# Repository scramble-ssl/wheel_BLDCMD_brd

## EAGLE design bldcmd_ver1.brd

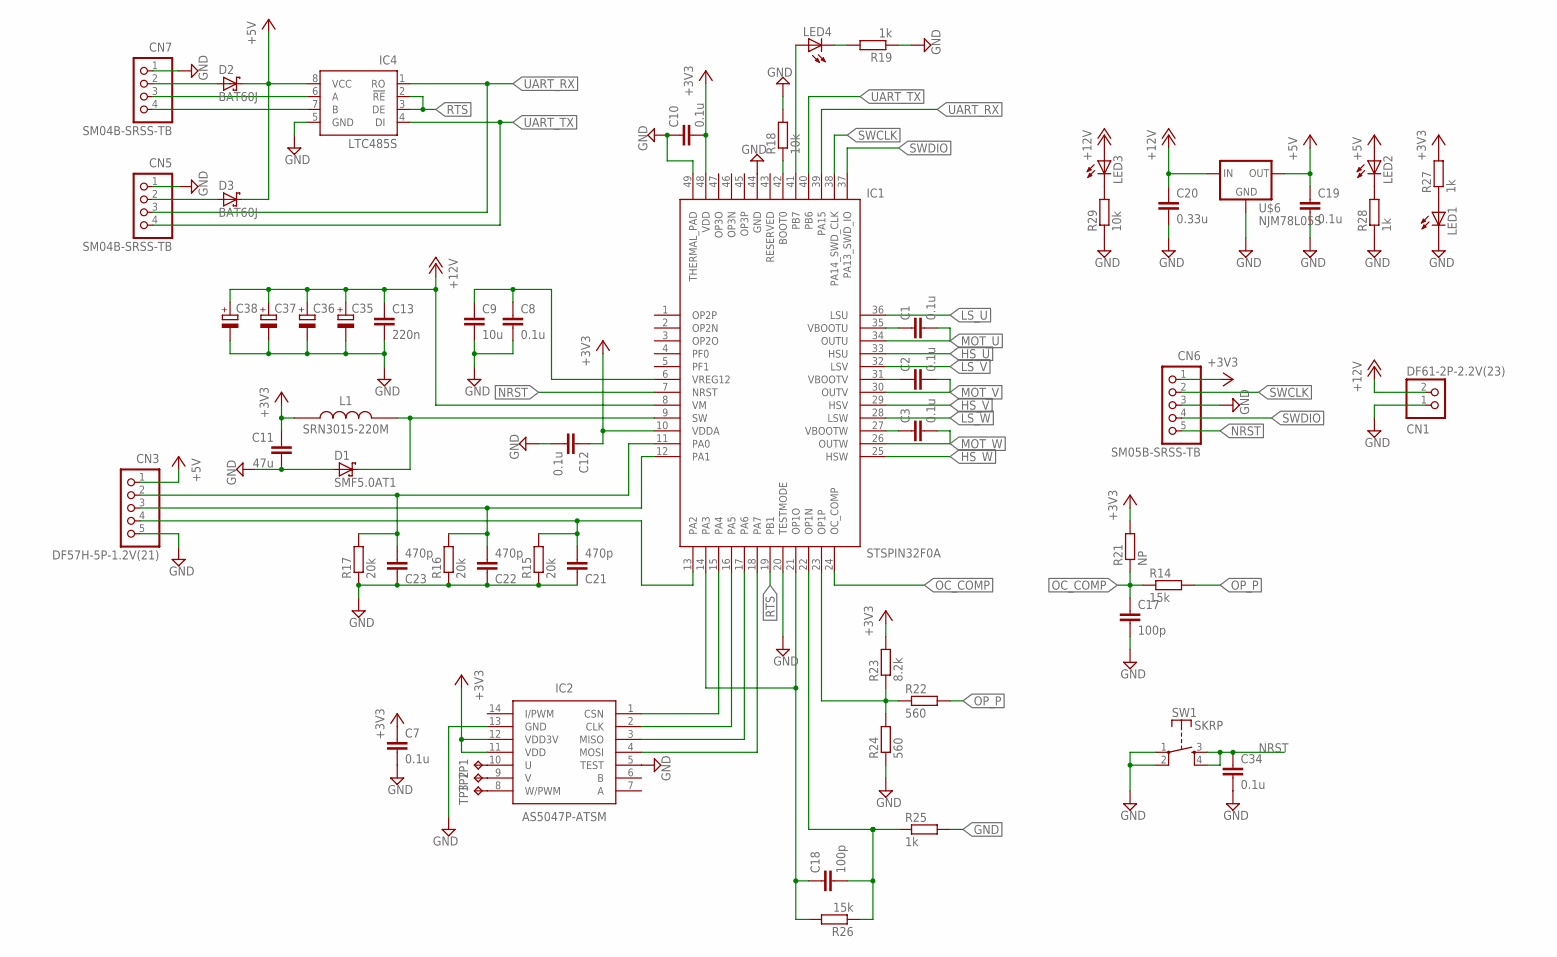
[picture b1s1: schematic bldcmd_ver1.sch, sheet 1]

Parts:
C1, C2, C3: 0.1u; C0402
C7, C8, C10, C12, C19, C34: 0.1u; C0603K
C9: 10u; C0805K
C11: 47u; C1206K
C13: 220n; C0805K
C17, C18: 100p; C0402
C20: 0.33u; C0805K
C21, C22, C23: 470p; C0402
C35, C36, C37, C38: CPOL-EU153CLV-0605; 153CLV-0605
CN1: DF61-2P-2.2V(23); DF61-2P-2.2V
CN3: DF57H-5P-1.2V(21)
CN5, CN7: SM04B-SRSS-TB
CN6: SM05B-SRSS-TB
D1: SMF5.0AT1; SOD123FL
D2, D3: BAT60J; SOD323_ST
IC1: STSPIN32F0A; VFQFPN48_7X7X1.0-48L
IC2: AS5047P-ATSM; SOP65P640X120-14N
IC4: LTC485S; SOIC8
L1: SRN3015-220M; SRN3015
LED1, LED2, LED3, LED4: LEDSML0603; SML0603
R14, R26: 15k; R0402
R15, R16, R17: 20k; R0402
R18: 10k; R0402
R19, R27, R28: 1k; R0603
R21: NP; R0402
R22, R24: 560; R0402
R23: 8.2k; R0402
R25: 1k; R0402
R29: 10k; R0603
SW1: SKRP
TP1, TP2, TP3: TPTP08R; TP08R
U$6: NJM78L05S; SOT89R

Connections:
+3V3: C7.1, C10.2, C11.1, C12.1, CN6.1, IC1.10 (VDDA), IC1.48 (VDD), IC2.11 (VDD), IC2.12 (VDD3V), L1.1, R21.2, R23.2, R27.2
+5V: C19.1, CN3.1, D2.C, D3.C, IC4.8 (VCC), LED2.A, U$6.2 (OUT)
+12V: C13.1, C20.1, C35.+, C36.+, C37.+, C38.+, CN1.2, IC1.8 (VM), LED3.A, U$6.1 (IN); also elsewhere on the board
GND: C7.2, C8.2, C9.2, C10.1, C11.2, C12.2, C13.2, C17.2, C19.2, C20.2, C21.1, C22.1, C23.1, C34.2, C35.-, C36.-, C37.-, C38.-, CN1.1, CN3.5, CN5.1, CN6.3, CN7.1, D1.A, IC1.20 (TESTMODE), IC1.44 (GND), IC1.49 (THERMAL_PAD), IC2.5 (TEST), IC2.13 (GND), IC4.5 (GND), LED1.C, R15.1, R16.1, R17.1, R18.2, R19.1, R24.1, R25.2, R28.1, R29.1, SW1.1, SW1.2, U$6.3 (GND), U$6.4 (GND); also elsewhere on the board
HS_U: IC1.33 (HSU); also elsewhere on the board
HS_V: IC1.29 (HSV); also elsewhere on the board
HS_W: IC1.25 (HSW); also elsewhere on the board
LS_U: IC1.36 (LSU); also elsewhere on the board
LS_V: IC1.32 (LSV); also elsewhere on the board
LS_W: IC1.28 (LSW); also elsewhere on the board
MOT_U: C1.2, IC1.34 (OUTU); also elsewhere on the board
MOT_V: C2.2, IC1.30 (OUTV); also elsewhere on the board
MOT_W: C3.2, IC1.26 (OUTW); also elsewhere on the board
unnamed: C3.1, IC1.27 (VBOOTW)
unnamed: IC2.10 (U), TP1.TP
unnamed: IC2.9 (V), TP2.TP
unnamed: C2.1, IC1.31 (VBOOTV)
unnamed: C1.1, IC1.35 (VBOOTU)
unnamed: IC2.8 (W/PWM), TP3.TP
unnamed: IC1.15 (PA4), IC2.1 (CSN)
unnamed: IC1.16 (PA5), IC2.2 (CLK)
unnamed: CN5.2, D3.A
unnamed: IC1.17 (PA6), IC2.3 (MISO)
unnamed: IC1.18 (PA7), IC2.4 (MOSI)
unnamed: D1.C, IC1.9 (SW), L1.2
unnamed: C8.1, C9.1, IC1.6 (VREG12)
unnamed: LED2.C, R28.2
unnamed: IC1.42 (BOOT0), R18.1
unnamed: C21.2, CN3.4, IC1.13 (PA2), R15.2
unnamed: C22.2, CN3.3, IC1.12 (PA1), R16.2
unnamed: C23.2, CN3.2, IC1.11 (PA0), R17.2
unnamed: IC1.23 (OP1P), R22.1, R23.1, R24.2
unnamed: C18.2, IC1.22 (OP1N), R25.1, R26.1
unnamed: C18.1, IC1.14 (PA3), IC1.21 (OP1O), R26.2
unnamed: CN7.3, IC4.6 (A)
unnamed: CN7.2, D2.A
unnamed: LED1.A, R27.1
unnamed: CN7.4, IC4.7 (B)
unnamed: LED4.C, R19.2
unnamed: LED3.C, R29.2
unnamed: IC1.41 (PB7), LED4.A
NRST: C34.1, CN6.5, IC1.7 (NRST), SW1.3, SW1.4
OC_COMP: C17.1, IC1.24 (OC_COMP), R14.1, R21.1
OP_P: R14.2, R22.2; also elsewhere on the board
RTS: IC1.19 (PB1), IC4.2 (!RE), IC4.3 (DE)
SWCLK: CN6.2, IC1.38 (PA14_SWD_CLK)
SWDIO: CN6.4, IC1.37 (PA13_SWD_IO)
UART_RX: CN5.3, IC1.39 (PA15), IC4.1 (RO)
UART_TX: CN5.4, IC1.40 (PB6), IC4.4 (DI)

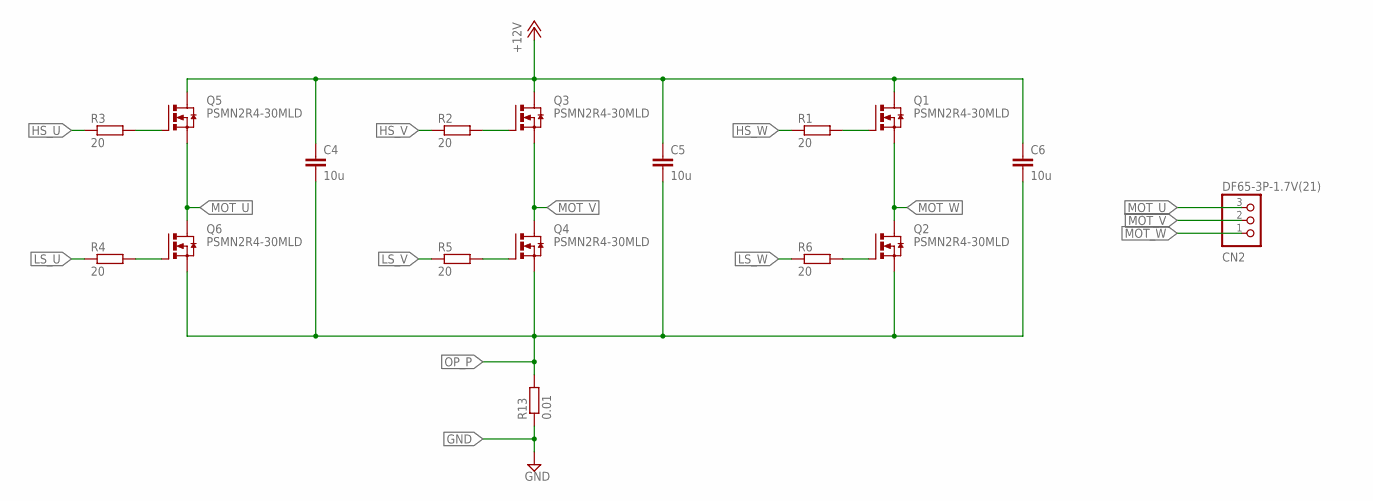
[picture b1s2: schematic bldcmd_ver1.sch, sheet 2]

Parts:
C4, C5, C6: 10u; C1206
CN2: DF65-3P-1.7V(21); DF65-3P-1.7V
Q1, Q2, Q3, Q4, Q5, Q6: PSMN2R4-30MLD; LFPAK33
R1, R2, R3, R4, R5, R6: 20; R0603
R13: 0.01; R3216

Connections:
+12V: C4.1, C5.1, C6.1, Q1.MB (D), Q3.MB (D), Q5.MB (D); also elsewhere on the board
GND: R13.1; also elsewhere on the board
HS_U: R3.1; also elsewhere on the board
HS_V: R2.1; also elsewhere on the board
HS_W: R1.1; also elsewhere on the board
LS_U: R4.1; also elsewhere on the board
LS_V: R5.1; also elsewhere on the board
LS_W: R6.1; also elsewhere on the board
MOT_U: CN2.3, Q5.1 (S), Q5.2 (S), Q5.3 (S), Q6.MB (D); also elsewhere on the board
MOT_V: CN2.2, Q3.1 (S), Q3.2 (S), Q3.3 (S), Q4.MB (D); also elsewhere on the board
MOT_W: CN2.1, Q1.1 (S), Q1.2 (S), Q1.3 (S), Q2.MB (D); also elsewhere on the board
unnamed: Q1.4 (G), R1.2
unnamed: Q3.4 (G), R2.2
unnamed: Q5.4 (G), R3.2
unnamed: Q6.4 (G), R4.2
unnamed: Q4.4 (G), R5.2
unnamed: Q2.4 (G), R6.2
OP_P: C4.2, C5.2, C6.2, Q2.1 (S), Q2.2 (S), Q2.3 (S), Q4.1 (S), Q4.2 (S), Q4.3 (S), Q6.1 (S), Q6.2 (S), Q6.3 (S), R13.2; also elsewhere on the board

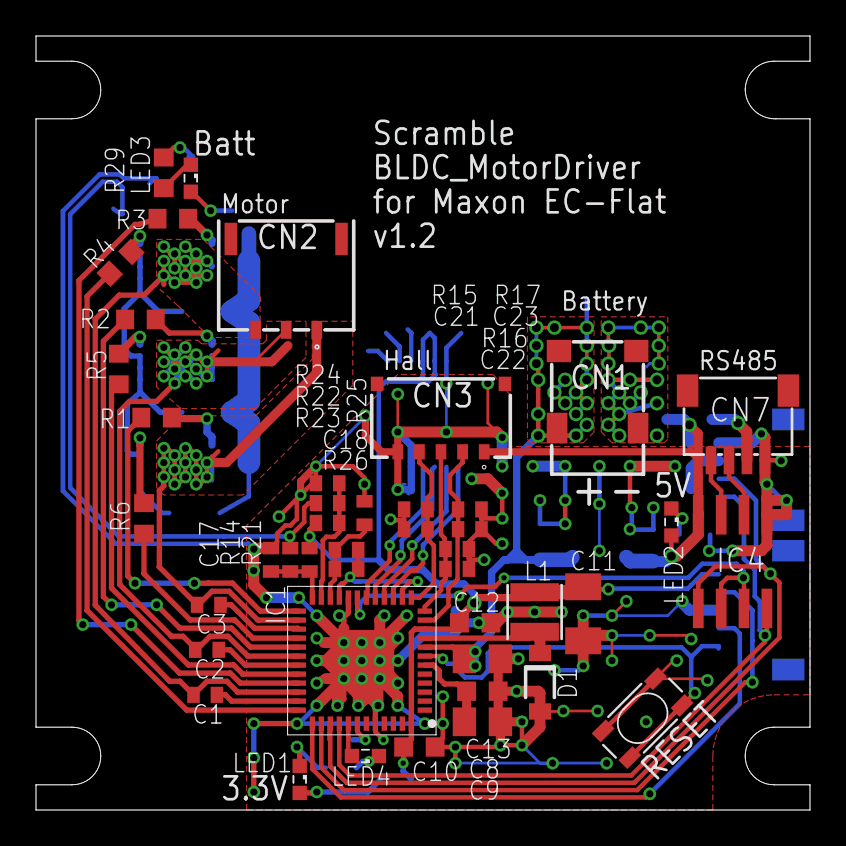
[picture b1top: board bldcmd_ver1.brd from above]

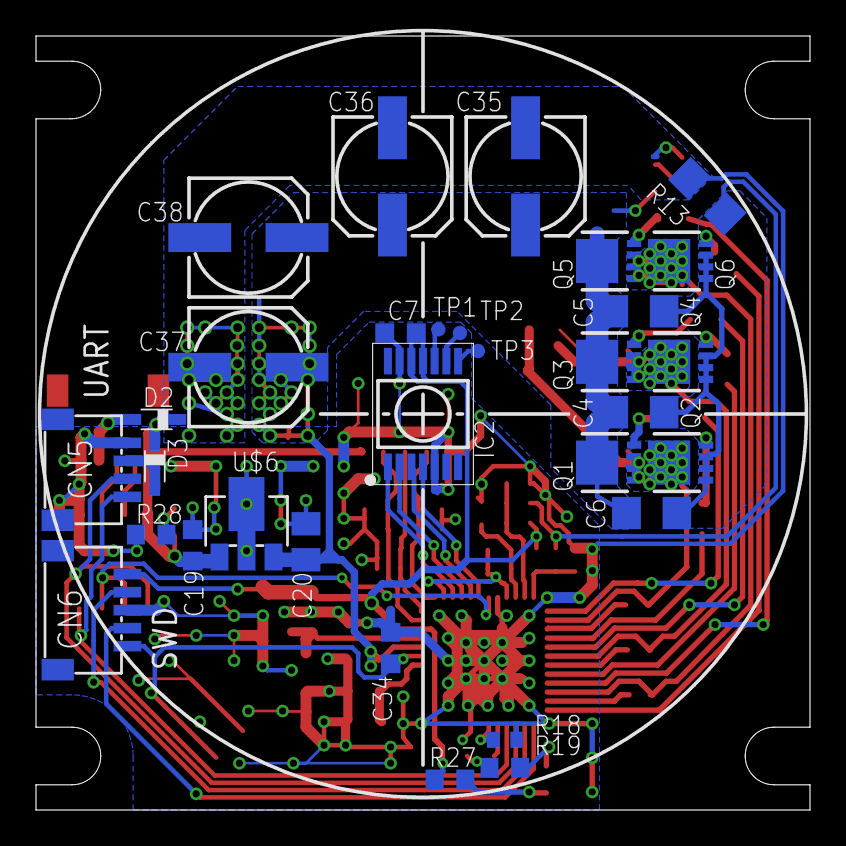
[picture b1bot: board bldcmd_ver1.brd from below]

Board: 2 copper layers, 43.0 x 43.0 mm, 75 parts (31 on the bottom side), 55 nets.

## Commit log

2017-09-10 MCUとブリッジ回路の部品配置
2017-09-10 磁気エンコーダAS5047P追加
2017-09-11 CスナバをGNDからローサイドFETのソースに接続変更
2017-09-12 部品追加
    RS485トランシーバ
    バックコンバータ用インダクタ
    パスコン
2017-09-12 部品追加
    モータ出力コネクタ
    ネジ穴
2017-09-17 ブリッジ回路AW攻めた
2017-09-19 現状乗っている部品はほぼ配線完了
2017-09-20 オペアンプつけた
2017-09-21 5Vレギュレータと電源LED追加
2017-09-22 コンデンサ増やした
2017-09-23 シルクの位置調整
2017-09-27 ホールセンサのLPFのR,Cのサイズを0402から0603に変更
2017-10-03 12Vのテストピンの削除 RSTスイッチの向きを変更
2017-10-03 コネクタとLEDにシルク追加
2017-11-12 電源コネクタをES9からDF61に変更
2017-11-13 DF61-2P-2.2V(23) の修正を適用
2017-11-13 DF65のライブラリ場所の変更を適用
2017-11-13 #2 の対応，MCUをstspin32F0Aに変更
2017-11-13 #3 の対応，エンコーダ入力からSPI接続に変更
2017-11-14 修正したSHコネクタの変更を適用
2017-11-15 ST-Linkのコネクタの接続順を入れ替えた
2017-11-22 3端子レギュレータのライブラリ変更の反映 SHコネクタの接続順を反転
2017-11-22 部品に必要な値を割り当てた，（最適なのか？） BOM出した
2017-11-23 AWを修正，コネクタの変更を適用
2017-11-23 シルクの修正 これで発注した
2017-12-05 差動レシーバのシルク位置修正（シルクの修正，発注とはなんだったのか）
2017-12-13 BSコンデンサを0402inchに変更 デバッグ用のLEDを追加 BOOT0のプルダウン抵抗の追加( #4)
2017-12-18 REG12のコンデンサの位置を調整
2017-12-27 RS485のICをSOIC8のものに変更
2018-01-08 AW進捗
2018-01-27 ゲートのプルダウン抵抗取り除いた AWをかなり攻めた
2018-01-28 基板サイズを変更した
2018-01-30 AW進捗，これで発注
2018-02-04 電解コンデンサのパターンを追加
2018-02-07 AW修正
2018-02-10 電源ラインのセラミックコンデンサ削除
2018-02-10 DF57のライブラリを更新たので適用
2018-02-21 fusion360と基板の同期
2018-05-04 Create LICENSE

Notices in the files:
parts and their libraries:
rcssl_lib: PSMN2R4-30MLDC ©  Nexperia B.V. 2017. All rights reserved
rcssl_lib: PSMN2R4-30MLD © Nexperia B.V. 2017. All rights reserved
